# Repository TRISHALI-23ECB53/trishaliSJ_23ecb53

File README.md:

View this project on [CADLAB.io](https://cadlab.io/project/29287). 

# trishaliSJ_23ecb53

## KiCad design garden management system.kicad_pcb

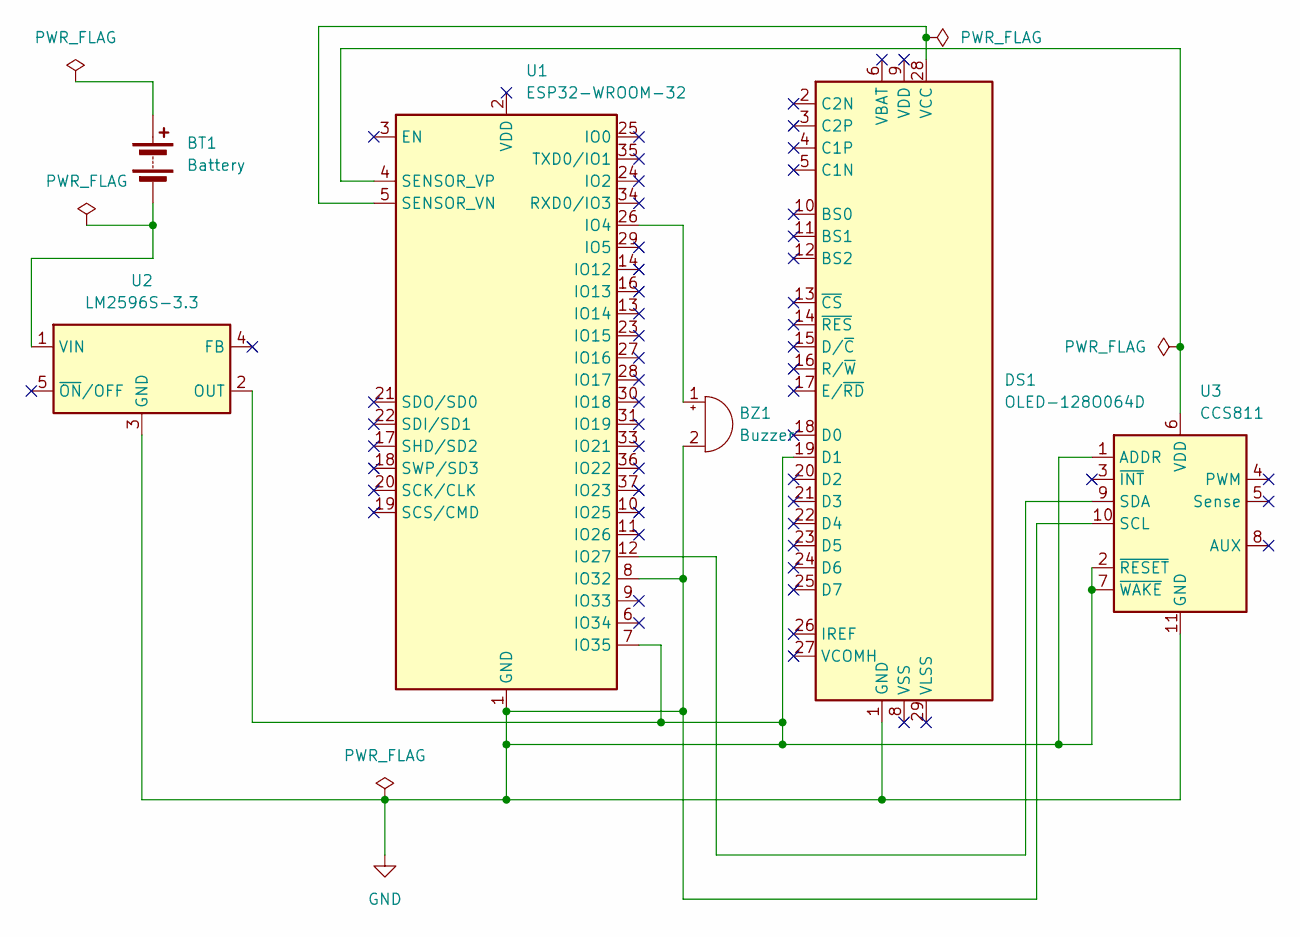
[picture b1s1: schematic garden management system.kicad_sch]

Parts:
BT1: Battery; BatteryHolder_Keystone_104_1x23mm
BZ1: Buzzer; Buzzer_D14mm_H7mm_P10mm
DS1: OLED-128O064D
U1: ESP32-WROOM-32; ESP32-WROOM-32E
U2: LM2596S-3.3; TO-263-5_TabPin3
U3: CCS811; AMS_LGA-10-1EP_2.7x4mm_P0.6mm

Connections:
GND: BZ1.2 (-), DS1.1 (GND), DS1.19 (D1), DS1.30 (GND), U1.1 (GND), U1.7 (IO35), U1.8 (IO32), U1.15 (GND), U1.38 (GND), U1.39 (GND), U2.2 (OUT), U2.3 (GND), U3.1 (ADDR), U3.2 (~RESET), U3.7 (~WAKE), U3.10 (SCL), U3.11 (GND)
unnamed: BT1.2 (-), U2.1 (VIN)
unnamed: BZ1.1 (+), U1.26 (IO4)
unnamed: DS1.28 (VCC), U1.5 (SENSOR_VN)
unnamed: U1.12 (IO27), U3.9 (SDA)
unnamed: U1.4 (SENSOR_VP), U3.6 (VDD)

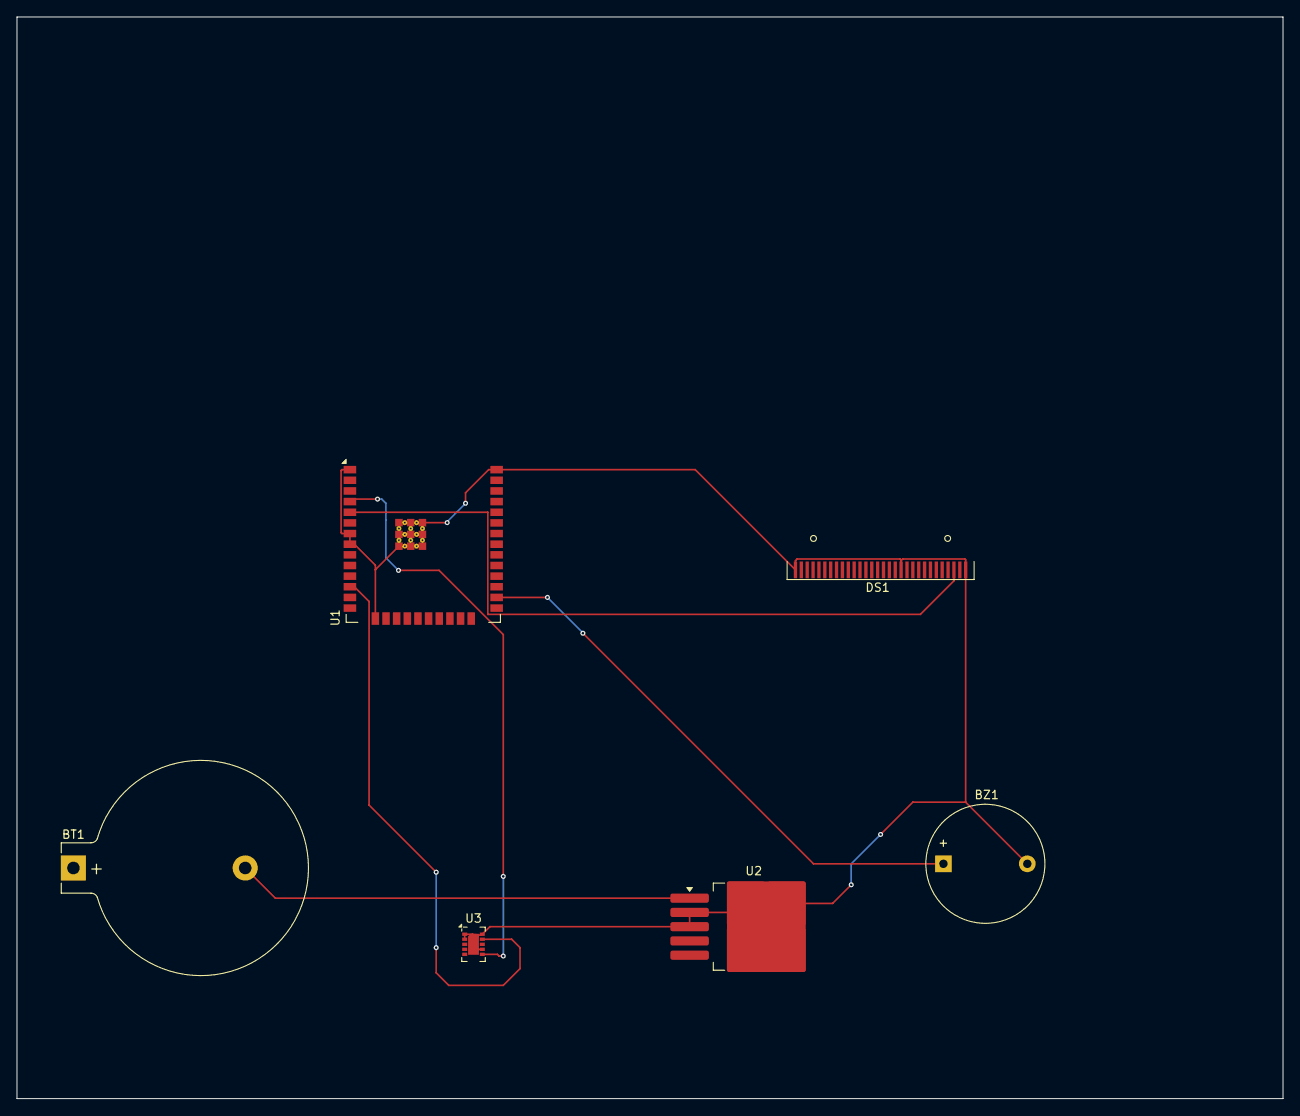
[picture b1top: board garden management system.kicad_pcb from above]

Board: 2 copper layers, 151.0 x 129.0 mm, 6 parts (0 on the bottom side), 6 nets.

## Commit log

2025-04-20 Backlink to CADLAB.io has been added.
